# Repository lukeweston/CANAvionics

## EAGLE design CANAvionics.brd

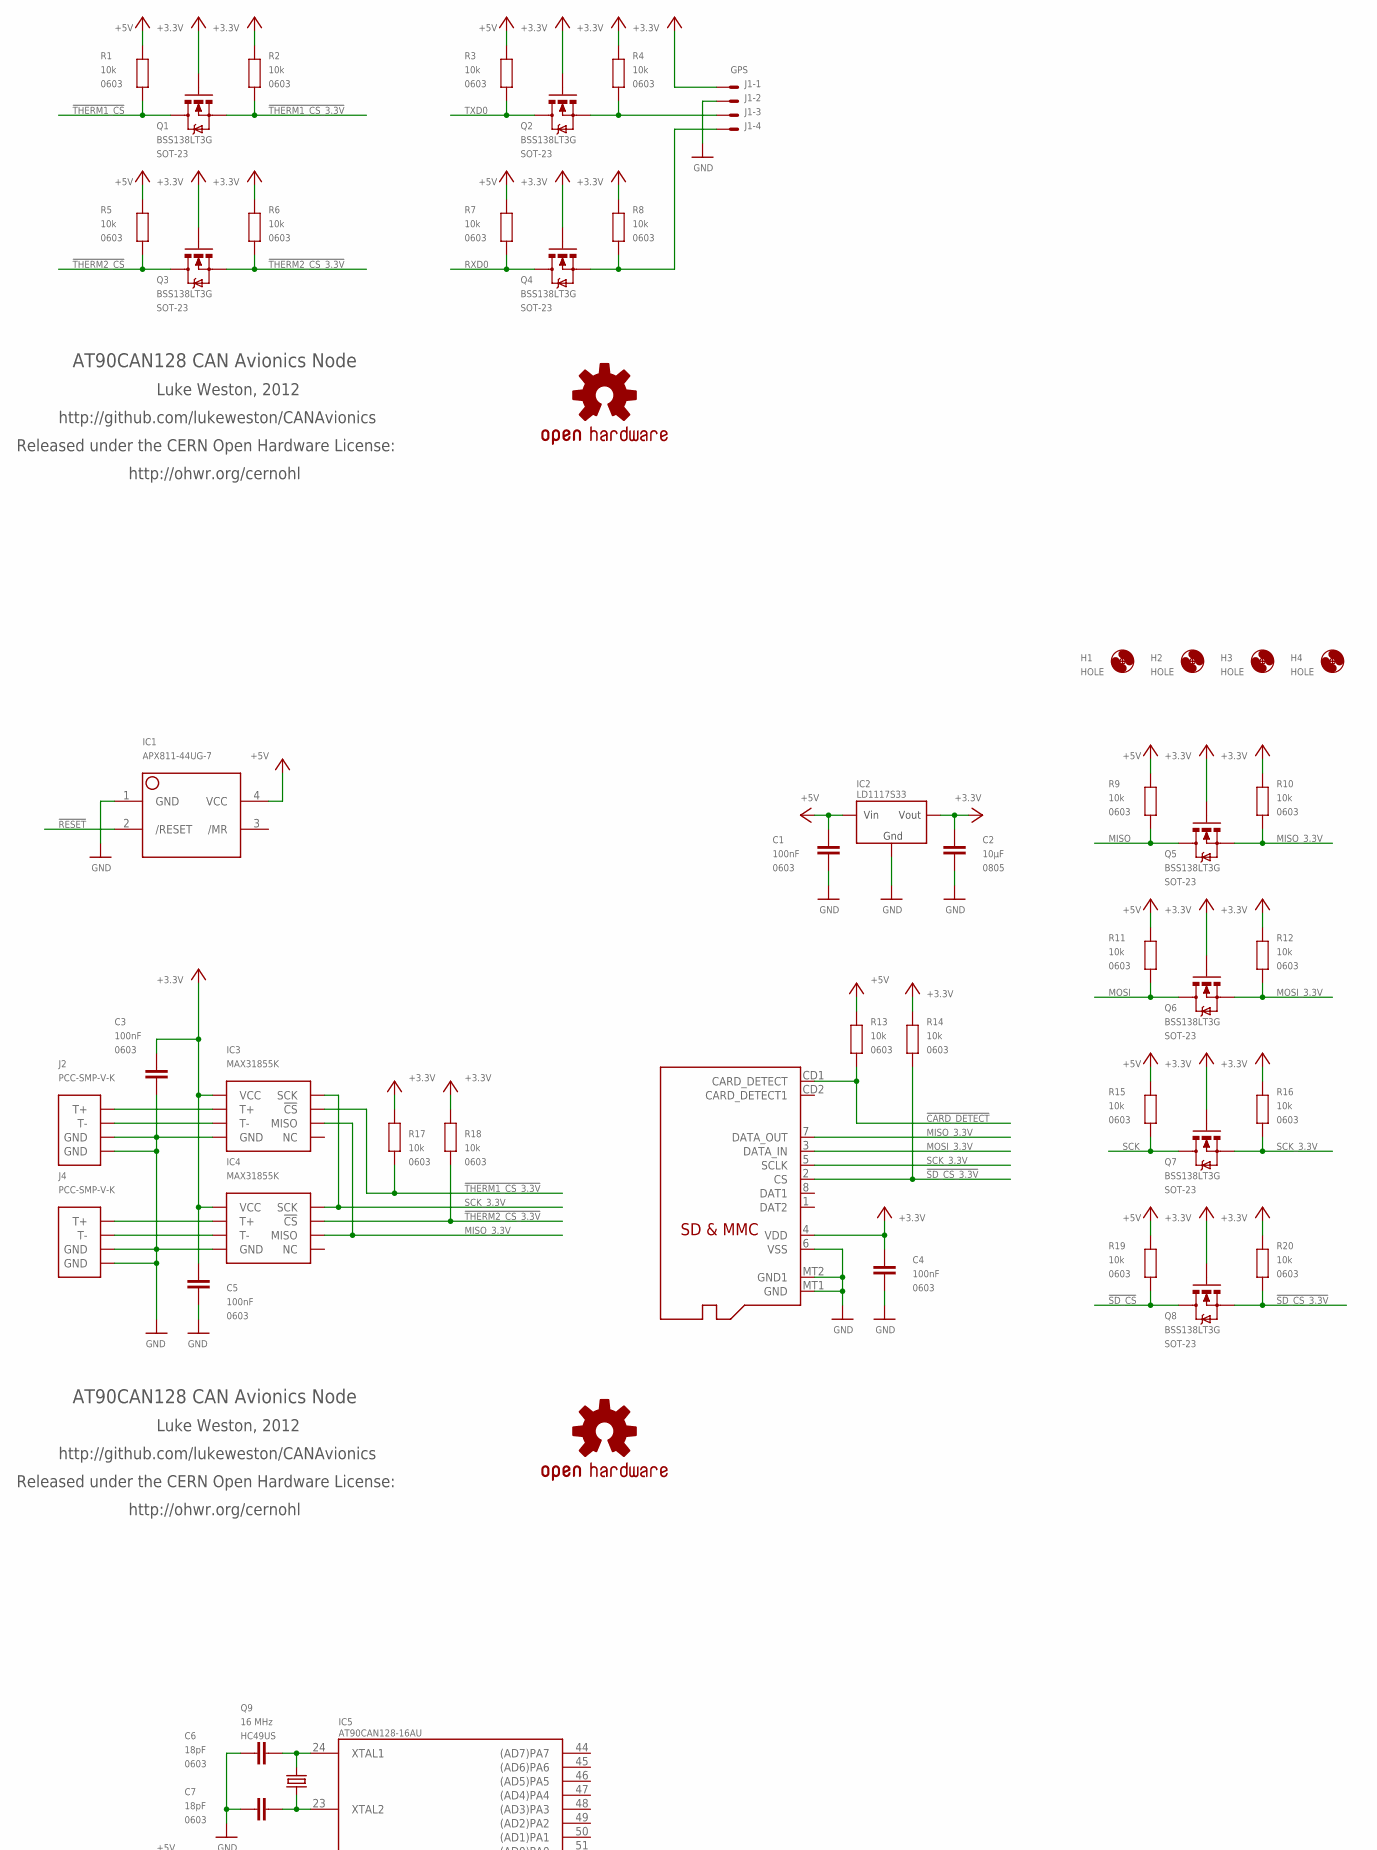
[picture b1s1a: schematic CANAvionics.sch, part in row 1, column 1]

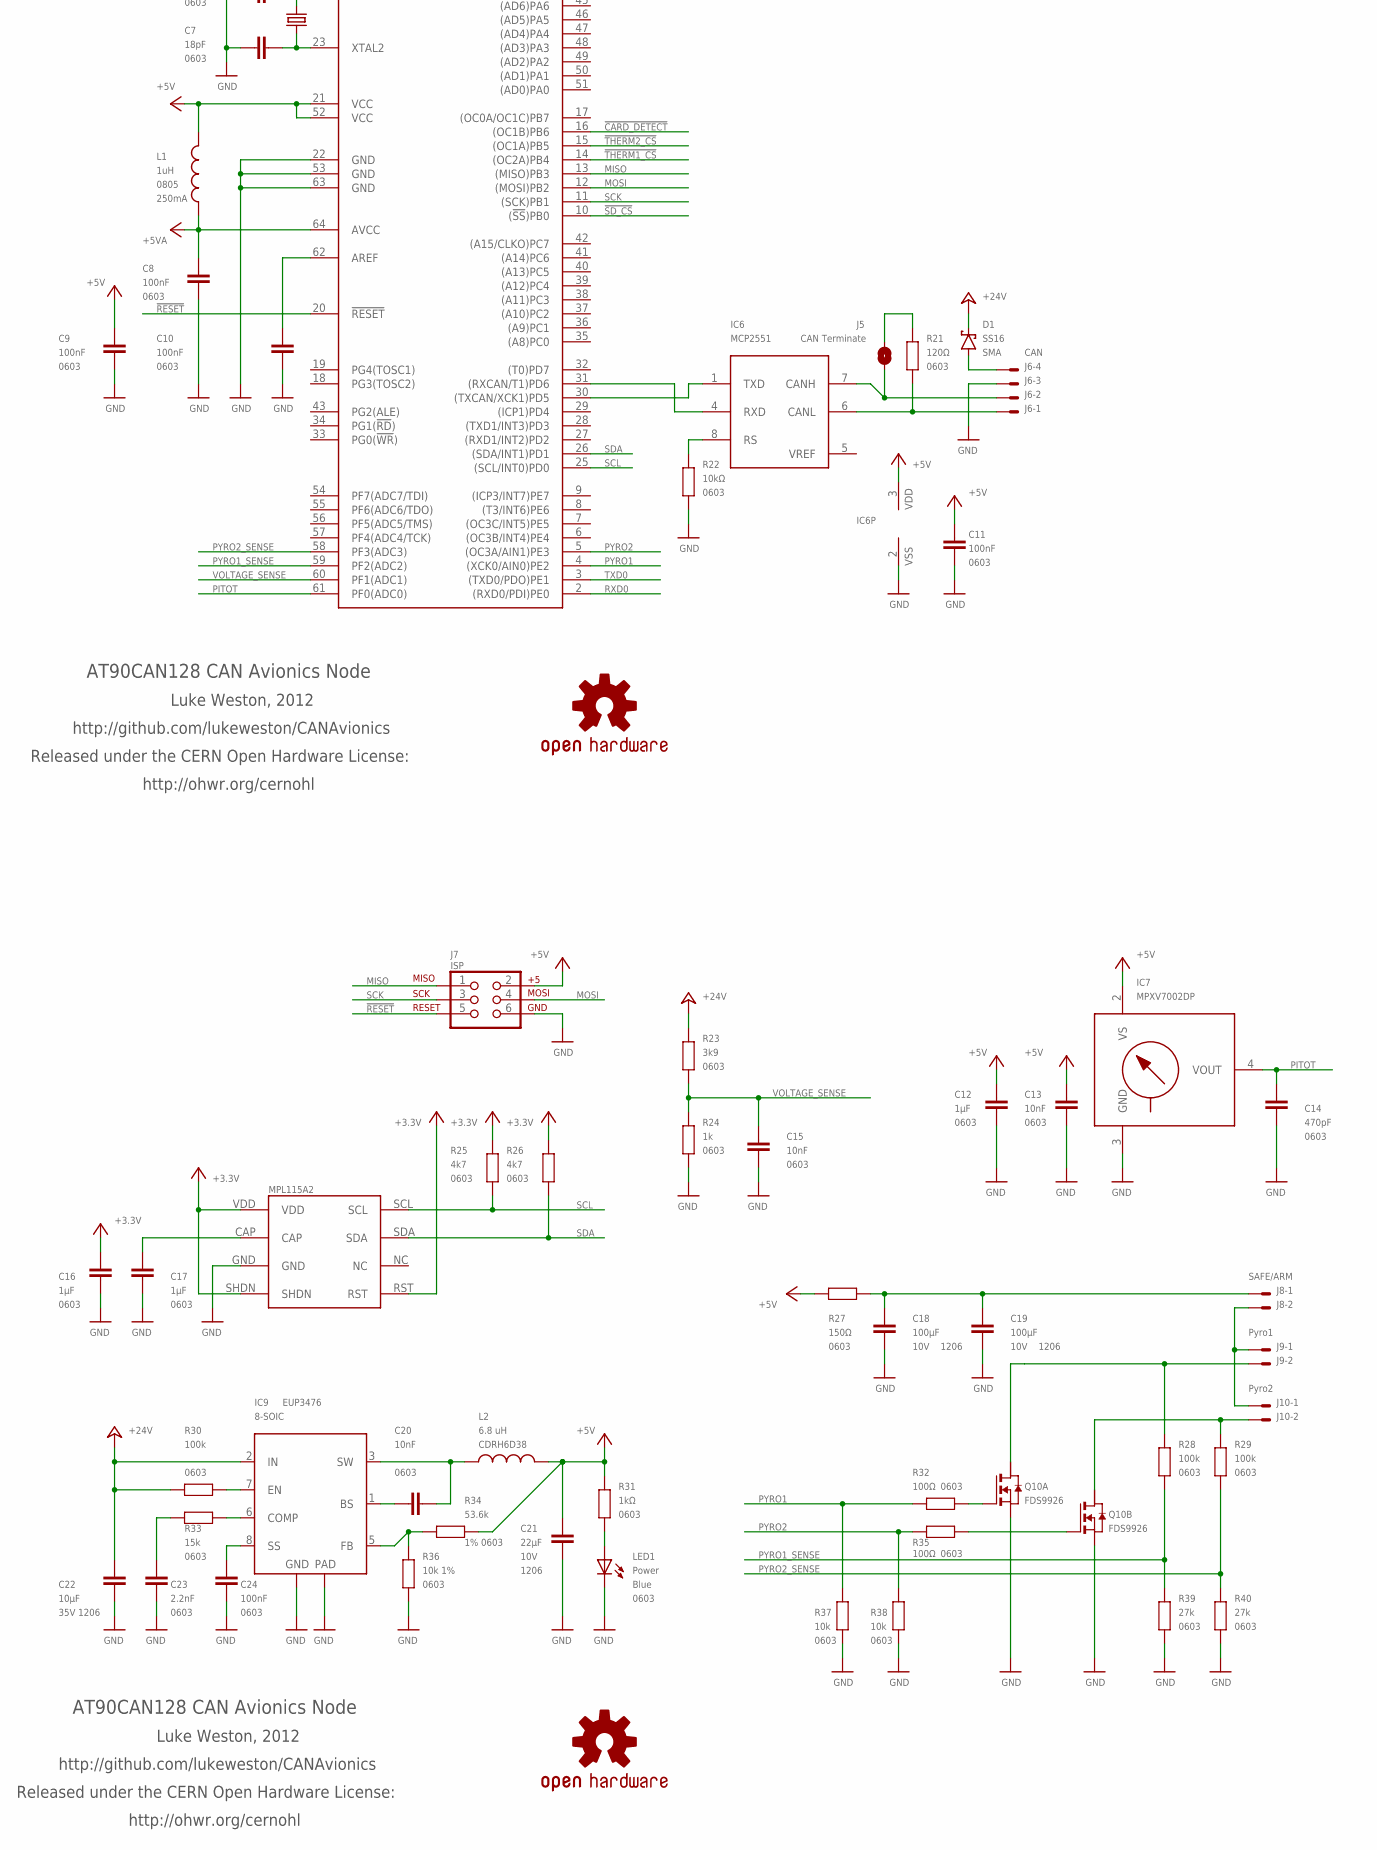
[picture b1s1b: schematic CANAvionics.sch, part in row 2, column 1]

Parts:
C1, C3, C4, C5, C8, C9, C10, C11, C24: 100nF; 0603
C2: 10µF; 0805
C6, C7: 18pF; 0603
C12, C16, C17: 1µF; 0603
C13, C15, C20: 10nF; 0603
C14: 470pF; 0603
C18, C19: 100µF; C1206K; VOLTAGE 10V
C21: 22µF; C1206K; VOLTAGE 10V
C22: 10µF; C1206K; VOLTAGE 35V 1206
C23: 2.2nF; 0603
D1: SS16; SMA
H1, H2, H3, H4: HOLE; 3,2
IC1: APX811-44UG-7; SOT143-R
IC2: LD1117S33; SOT223
IC3, IC4: MAX31855K; MCLENG_SOIC-8
IC5: AT90CAN128-16AU; TQFP64-0.8MM
IC6: MCP2551; SO-08
IC7: MPXV7002DP; 1351
IC8: MPL115A
IC9: EUP3476; SO08T
J1: GPS; 7395-04
J2, J4: PCC-SMP-V-K; MCLAUGHLINENG_TC_JACK
J3: MicroSD Card; ADAFRUIT_MICROSD
J5: CAN Terminate; SJ
J6: CAN; 7395-04
J7: ISP; 2X3
J8: SAFE/ARM; 7395-02
J9: Pyro1; 7395-02
J10: Pyro2; 7395-02
L1: 1uH; L2012C
L2: 6.8 uH; CDRH
LED1: Power; LED-0603
Q1, Q2, Q3, Q4, Q5, Q6, Q7, Q8: BSS138LT3G; SOT23-3
Q9: 16 MHz; HC49US
Q10: FDS9926; SM8
R1, R2, R3, R4, R5, R6, R7, R8, R9, R10, R11, R12, R13, R14, R15, R16, R17, R18, R19, R20, R37, R38: 10k; 0603
R21: 120Ω; 0603
R22: 10kΩ; 0603
R23: 3k9; 0603
R24: 1k; 0603
R25, R26: 4k7; 0603
R27: 150Ω; 0603
R28, R29, R30: 100k; 0603
R31: 1kΩ; 0603
R32, R35: 100Ω; 0603
R33: 15k; 0603
R34: 53.6k; 0603
R36: 10k 1%; 0603
R39, R40: 27k; 0603
SY1, SY2, SY3, SY4: OSHW-LOGOS; OSHW-LOGO-S

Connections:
!CARD_DETECT: IC5.16 ((OC1B)PB6), J3.CD1 (CARD_DETECT), R13.2
!RESET: IC1.2 (/RESET), IC5.20 (!RESET), J7.5
!SD_CS: IC5.10 ((!SS!)PB0), Q8.3 (D), R19.1
!SD_CS_3.3V: J3.2 (CS), Q8.2 (S), R14.2, R20.1
!THERM1_CS: IC5.14 ((OC2A)PB4), Q1.3 (D), R1.1
!THERM1_CS_3.3V: IC3.CS (!CS), Q1.2 (S), R2.1, R17.2
!THERM2_CS: IC5.15 ((OC1A)PB5), Q3.3 (D), R5.1
!THERM2_CS_3.3V: IC4.CS (!CS), Q3.2 (S), R6.1, R18.2
+3V3: C2.2, C3.2, C4.2, C5.1, C16.2, IC2.2 (VOUT), IC3.VCC, IC4.VCC, IC8.RST, IC8.SHDN, IC8.VDD, J1.1, J3.4 (VDD), Q1.1 (G), Q2.1 (G), Q3.1 (G), Q4.1 (G), Q5.1 (G), Q6.1 (G), Q7.1 (G), Q8.1 (G), R2.2, R4.2, R6.2, R8.2, R10.2, R12.2, R14.1, R16.2, R17.1, R18.1, R20.2, R25.2, R26.2
+5V: C1.2, C9.2, C11.2, C12.2, C13.2, C21.1, IC1.4 (VCC), IC2.3 (VIN), IC5.21 (VCC), IC5.52 (VCC), IC6.3 (VDD), IC7.2 (VS), J7.2, L1.1, L2.2, R1.2, R3.2, R5.2, R7.2, R9.2, R11.2, R13.1, R15.2, R19.2, R27.2, R31.1, R34.1
+5VA: C8.2, IC5.64 (AVCC), L1.2
+24V: C22.1, D1.K, IC9.2 (IN), R23.2, R30.2
CANH: IC6.7 (CANH), J5.2, J6.2
CANL: IC6.6 (CANL), J6.1, R21.1
GND: C1.1, C2.1, C3.1, C4.1, C5.2, C6.1, C7.1, C8.1, C9.1, C10.1, C11.1, C12.1, C13.1, C14.1, C15.1, C16.1, C17.1, C18.1, C19.1, C21.2, C22.2, C23.1, C24.1, IC1.1 (GND), IC2.1 (GND), IC3.GND, IC4.GND, IC5.22 (GND), IC5.53 (GND), IC5.63 (GND), IC6.2 (VSS), IC7.3 (GND), IC8.GND, IC9.4 (GND), IC9.9 (TGND), J1.2, J2.P$1 (GND), J2.P$2 (GND), J3.6 (VSS), J3.MT1 (GND), J3.MT2 (GND1), J4.P$1 (GND), J4.P$2 (GND), J6.3, J7.6, LED1.C, Q10.1 (S), Q10.3 (S), R22.2, R24.1, R36.2, R37.2, R38.2, R39.1, R40.1
GPS_RXD: J1.3, Q2.2 (S), R4.1
GPS_TXD: J1.4, Q4.2 (S), R8.1
MISO: IC5.13 ((MISO)PB3), J7.1, Q5.3 (D), R9.1
MISO_3.3V: IC3.SO (MISO), IC4.SO (MISO), J3.7 (DATA_OUT), Q5.2 (S), R10.1
MOSI: IC5.12 ((MOSI)PB2), J7.4, Q6.3 (D), R11.1
MOSI_3.3V: J3.3 (DATA_IN), Q6.2 (S), R12.1
unnamed: C17.2, IC8.CAP
unnamed: J10.2, Q10.7 (D), R29.2
unnamed: J9.2, Q10.5 (D), R28.2
unnamed: Q10.4 (G), R32.1
unnamed: Q10.2 (G), R35.1
unnamed: IC5.31 ((RXCAN/T1)PD6), IC6.4 (RXD)
unnamed: IC5.30 ((TXCAN/XCK1)PD5), IC6.1 (TXD)
unnamed: J8.2, J9.1, J10.1
unnamed: LED1.A, R31.2
unnamed: C18.2, C19.2, J8.1, R27.1
unnamed: C10.2, IC5.62 (AREF)
unnamed: C6.2, IC5.24 (XTAL1), Q9.2
unnamed: C7.2, IC5.23 (XTAL2), Q9.1
unnamed: IC4.T-, J4.T-
unnamed: IC4.T+, J4.T+
unnamed: D1.A, J6.4
unnamed: J5.1, R21.2
unnamed: IC3.T-, J2.T-
unnamed: IC3.T+, J2.T+
unnamed: IC9.7 (EN), R30.1
unnamed: C20.1, IC9.3 (SW), L2.1
unnamed: C20.2, IC9.1 (BS)
unnamed: C23.2, R33.2
unnamed: IC9.6 (COMP), R33.1
unnamed: C24.2, IC9.8 (SS)
unnamed: IC9.5 (FB), R34.2, R36.1
unnamed: IC6.8 (RS), R22.1
PITOT: C14.2, IC5.61 (PF0(ADC0)), IC7.4 (VOUT)
PYRO1: IC5.4 ((XCK0/AIN0)PE2), R32.2, R37.1
PYRO1_SENSE: IC5.59 (PF2(ADC2)), R28.1, R39.2
PYRO2: IC5.5 ((OC3A/AIN1)PE3), R35.2, R38.1
PYRO2_SENSE: IC5.58 (PF3(ADC3)), R29.1, R40.2
RXD0: IC5.2 ((RXD0/PDI)PE0), Q4.3 (D), R7.1
SCK: IC5.11 ((SCK)PB1), J7.3, Q7.3 (D), R15.1
SCK_3.3V: IC3.SCK, IC4.SCK, J3.5 (SCLK), Q7.2 (S), R16.1
SCL: IC5.25 ((SCL/INT0)PD0), IC8.SCL, R25.1
SDA: IC5.26 ((SDA/INT1)PD1), IC8.SDA, R26.1
TXD0: IC5.3 ((TXD0/PDO)PE1), Q2.3 (D), R3.1
VOLTAGE_SENSE: C15.2, IC5.60 (PF1(ADC1)), R23.1, R24.2
VREF: IC6.5 (VREF)

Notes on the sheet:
MPL115A2
AT90CAN128 CAN Avionics Node
Luke Weston, 2012
http://github.com/lukeweston/CANAvionics
Released under the CERN Open Hardware License:
http://ohwr.org/cernohl

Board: 2 copper layers, 105 parts (0 on the bottom side), 60 nets, no tracks yet.
